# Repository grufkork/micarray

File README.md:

# 16-channel Microphone Array for Spatial Audio Recording
This is an inexpensive 16-channel MEMS microphone array for recording spatial audio made in KiCad 8.0. It can  be used for creating immersive audio/video content, locating mechanical faults, tracking moving objects in a room and more.

This design is developed for the [Build-Your-Own Ambisonic Microphone Arrays](https://github.com/AppliedAcousticsChalmers/ambisonic-microphone-arrays) project, where you can also find more information regarding processing of the resulting recordings.

The array consists of four identical boards connected in a circle, allowing for low manufacturing costs (<100$ total, assembly included). These are then placed around an acoustically occluding sphere, emulating a persons head and allowing for generating realistic spatial audio. 

The array is connected to the [MiniDSP MCHStreamer Lite](https://www.minidsp.com/products/usb-audio-interface/mchstreamer-lite) sound card which receives and digitises the 8x PDM output (the non-lite version should work too, but has not been tested). 

### File structure

| Directory           | Contents                                                                                                      |
| ------------------- | ------------------------------------------------------------------------------------------------------------- |
| micarray            | 16ch microphone array, main design. Contains KiCAD project files and some exported models and visualisations. |
| imgs                | Images for this document                                                                                      |
| micarray_8ch_camera | Unfinished 8ch version for a 360° camera.                                                                     |
| 3dcammodel          | 3D-scan of 360° camera and visualisations                                                                     |

### Ordering
Production files are generated using [JLC Fabrication Toolkit](https://github.com/bennymeg/Fabrication-Toolkit) plugin for KiCad 8.0. All parts have `LCSC Part #`-fields so they can be assembled by JLC, but I would still recommend double checking everything, in particular small & cheap components so they have not gotten low availability. The full array consists of 4 quarter pieces connected in a circle. JLC minimum order size is 5, but having an extra module at hand has proven to be useful as all our orders have always had one mic with worsened performance. Whether this is due to JLC:s manufacturing process, errors in manufacturing, damages during transport or just bad luck is not known.

### Assembly
#### Shortening the inter-board headers
*This part is not mandatory for basic function, but if you want a precise, snug fit with exact distances between each microphone it is required. There will otherwise be a small gap between each board. **

Due to the tight space constraints, the headers connecting the boards to each other need to be trimmed. First remove the plastic holding the male header pins together, preferably by locally applying heat with a hot air gun and with pliers gently but decisively sliding the softened plastic off along the pins. Using a soldering iron or similar to try to melt plastic off is not recommended, as the residual plastic will fuse with the pins and form a thin insulating surface, which then needs to be sanded off. Be carful trying to cut the plastic into smaller parts, as this might bend the pins.

You can then try connecting the boards, noting how large the gap between them is (should be a couple of millimeters). Disconnect the boards and clip off the male pins so that the boards connect flush, edge-to-edge.

#### Connecting to the MCHStreamer
On each of the boards there is a vertical 2mm 12-pin header. This is to be connected to J3 on the MCHStreamer (check page 2 of [the datasheet](https://www.minidsp.com/images/documents/Product%20Brief-MCHStreamer%20Lite.pdf)). Note how the pins are mirrored, so they can be connected "towards" each other. As such, a 2x6 pin cable can be used. Which header is used only affects which mic is #1. Specifically, the first mic on the board opposite the connector will be channel 1. 

To interface with the array, upload the 16ch PDM firmware to the MCHStreamer. 

### Technical & Mechanical Details
The 16 mics are evenly spaced in a circle with 60.743mm radius. The array is made to fit on a 60mm sphere. The M3 mounting holes are 71.692mm out, 3.2mm in diameter, 27.1° counter-clockwise relative board edge.

The mics used are the Infineon IM73D122V01. They appear to currently be the best-performing MEMS mics available, using a novel double-membrane technology. Frustratingly, these have a slightly larger footprint with a different pad order than most other similar MEMS mics on the market, so be wary if swapping them for a different model.

The `stable` branch is the main, cleaned-up version of the old development `shrinkening` branch. 

### Troubleshooting
The primary problem you may experience is massive amounts of noise on one or several channels. This appears to be caused by the clock signal from the MCHStreamer ringing (overshooting) strongly. To prevent this, a 150pF capacitor is included in the design, connected between ground and the clock input. However, if you are still experiencing problems, soldering on some additional capacitance between `GND` and `PDM_CLK-IN` on the backside of one of the inter-board headers should resolve the issue. This fix is visible in the second image above, being the two yellow wires sticking out from one of the connectors.

## 8ch version
The 8ch version is an old, untested version of the 16ch for recording spatial audio with a 360° camera. It is not tested, but might work with some extra capacitance between `GND` and `PDM_CLK-IN`.

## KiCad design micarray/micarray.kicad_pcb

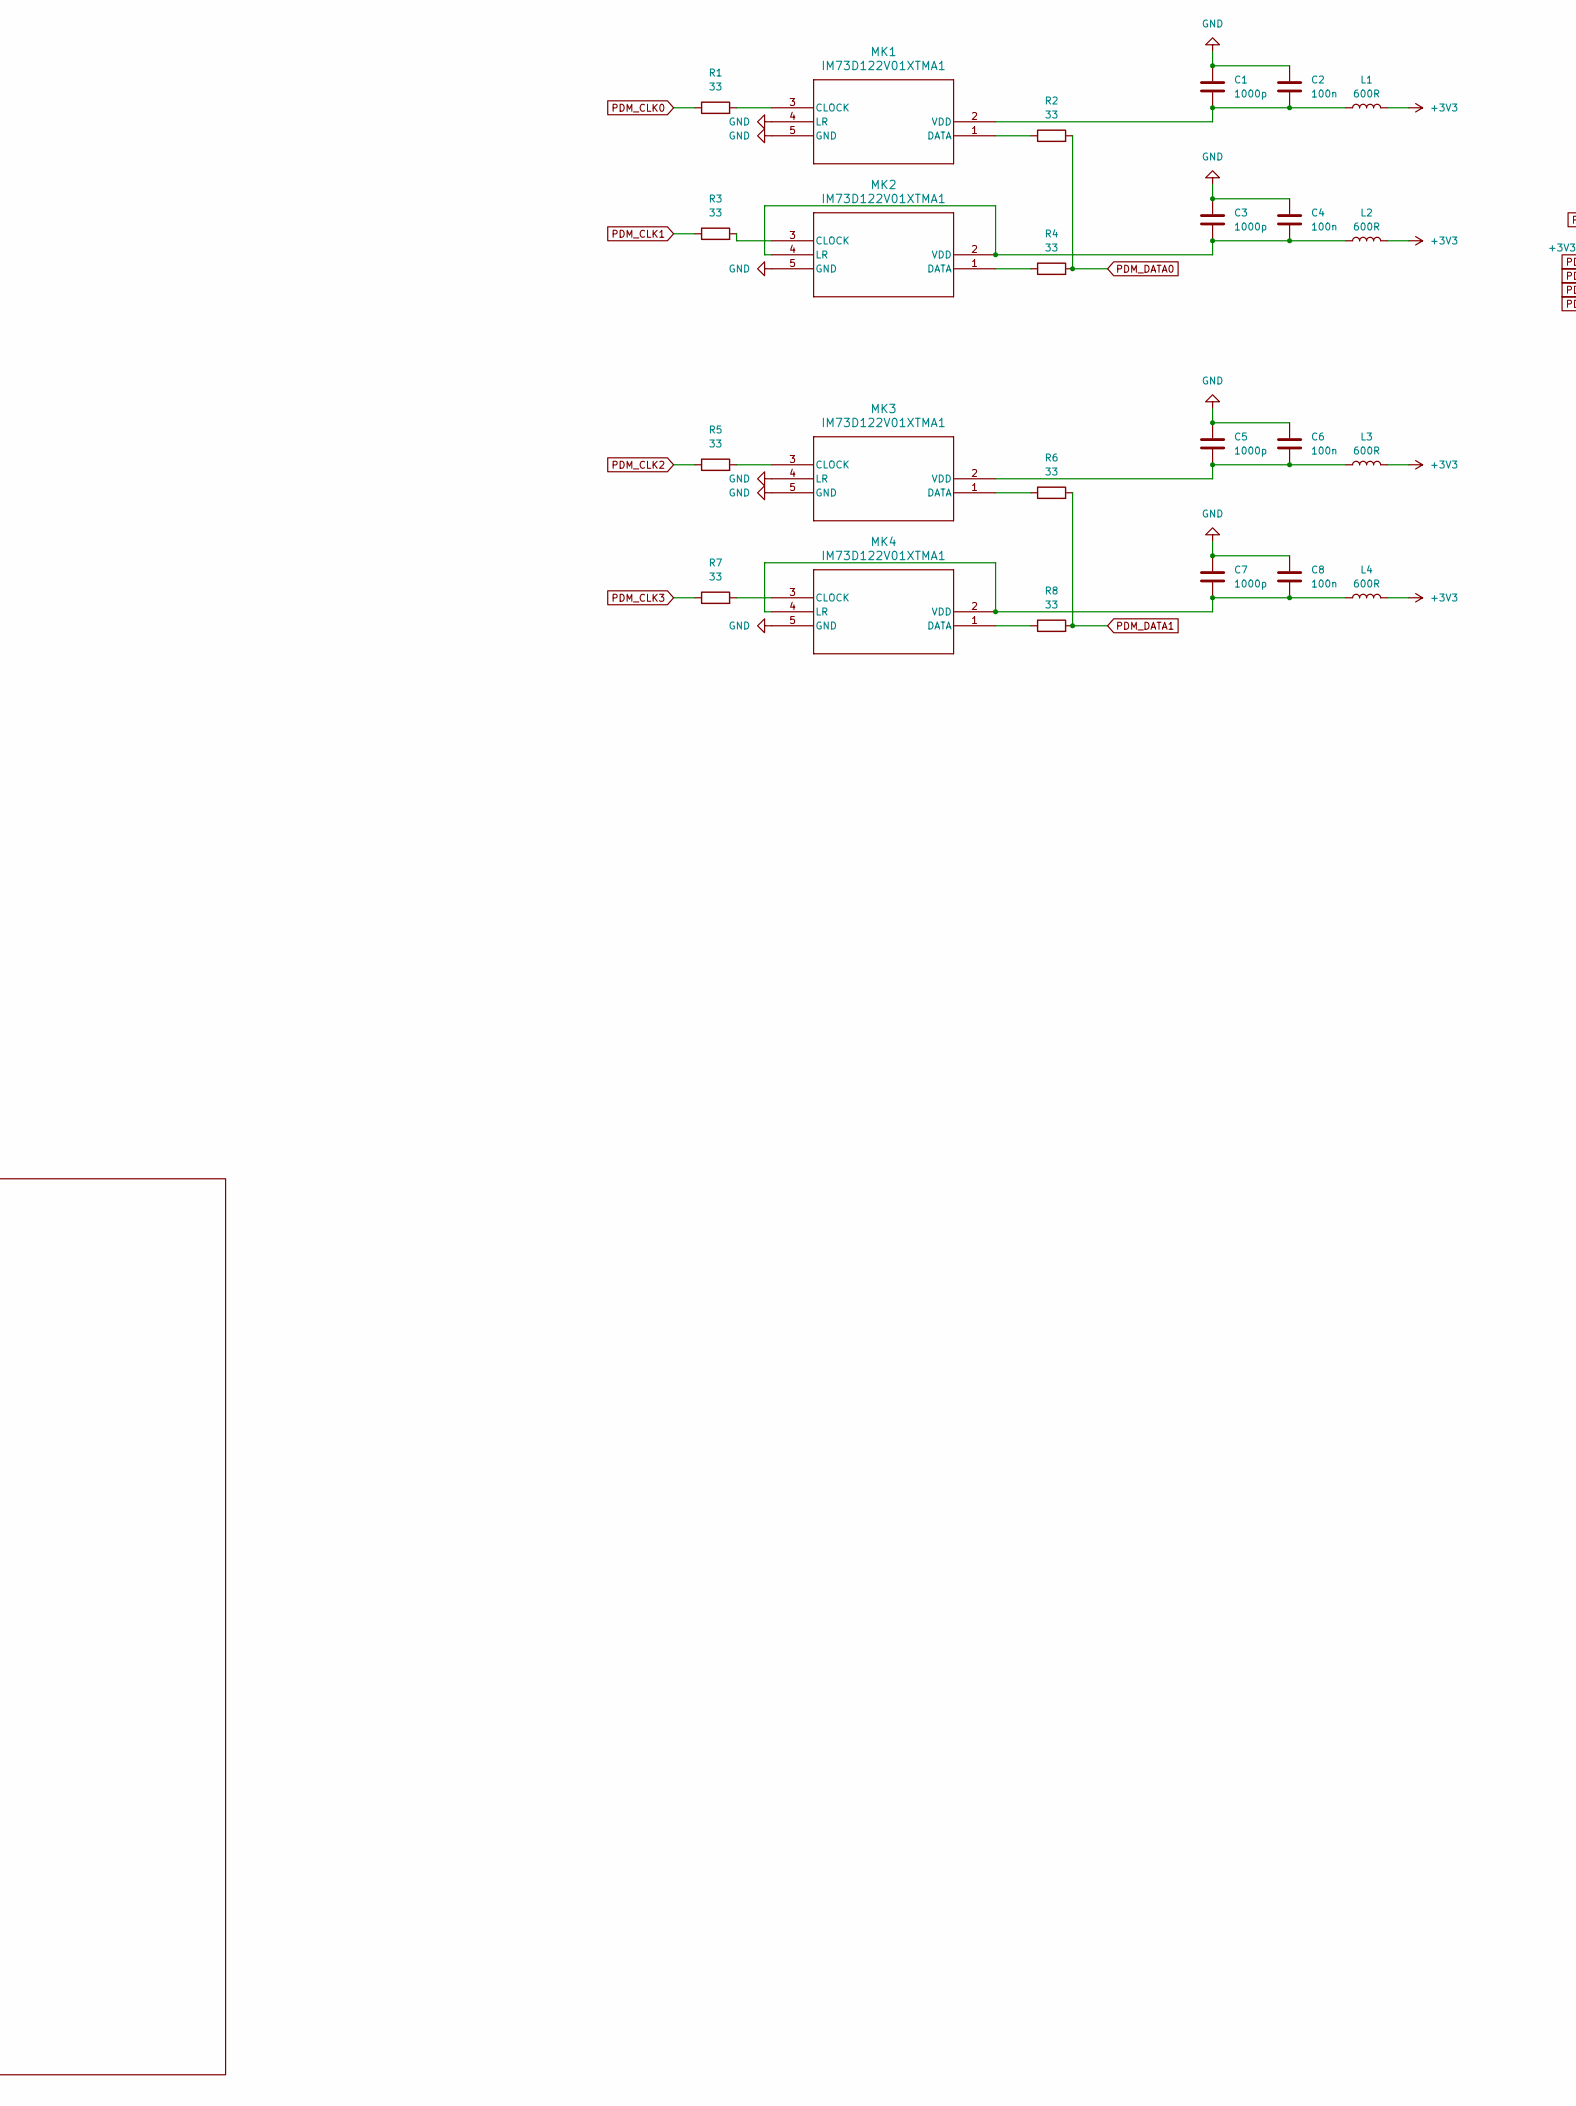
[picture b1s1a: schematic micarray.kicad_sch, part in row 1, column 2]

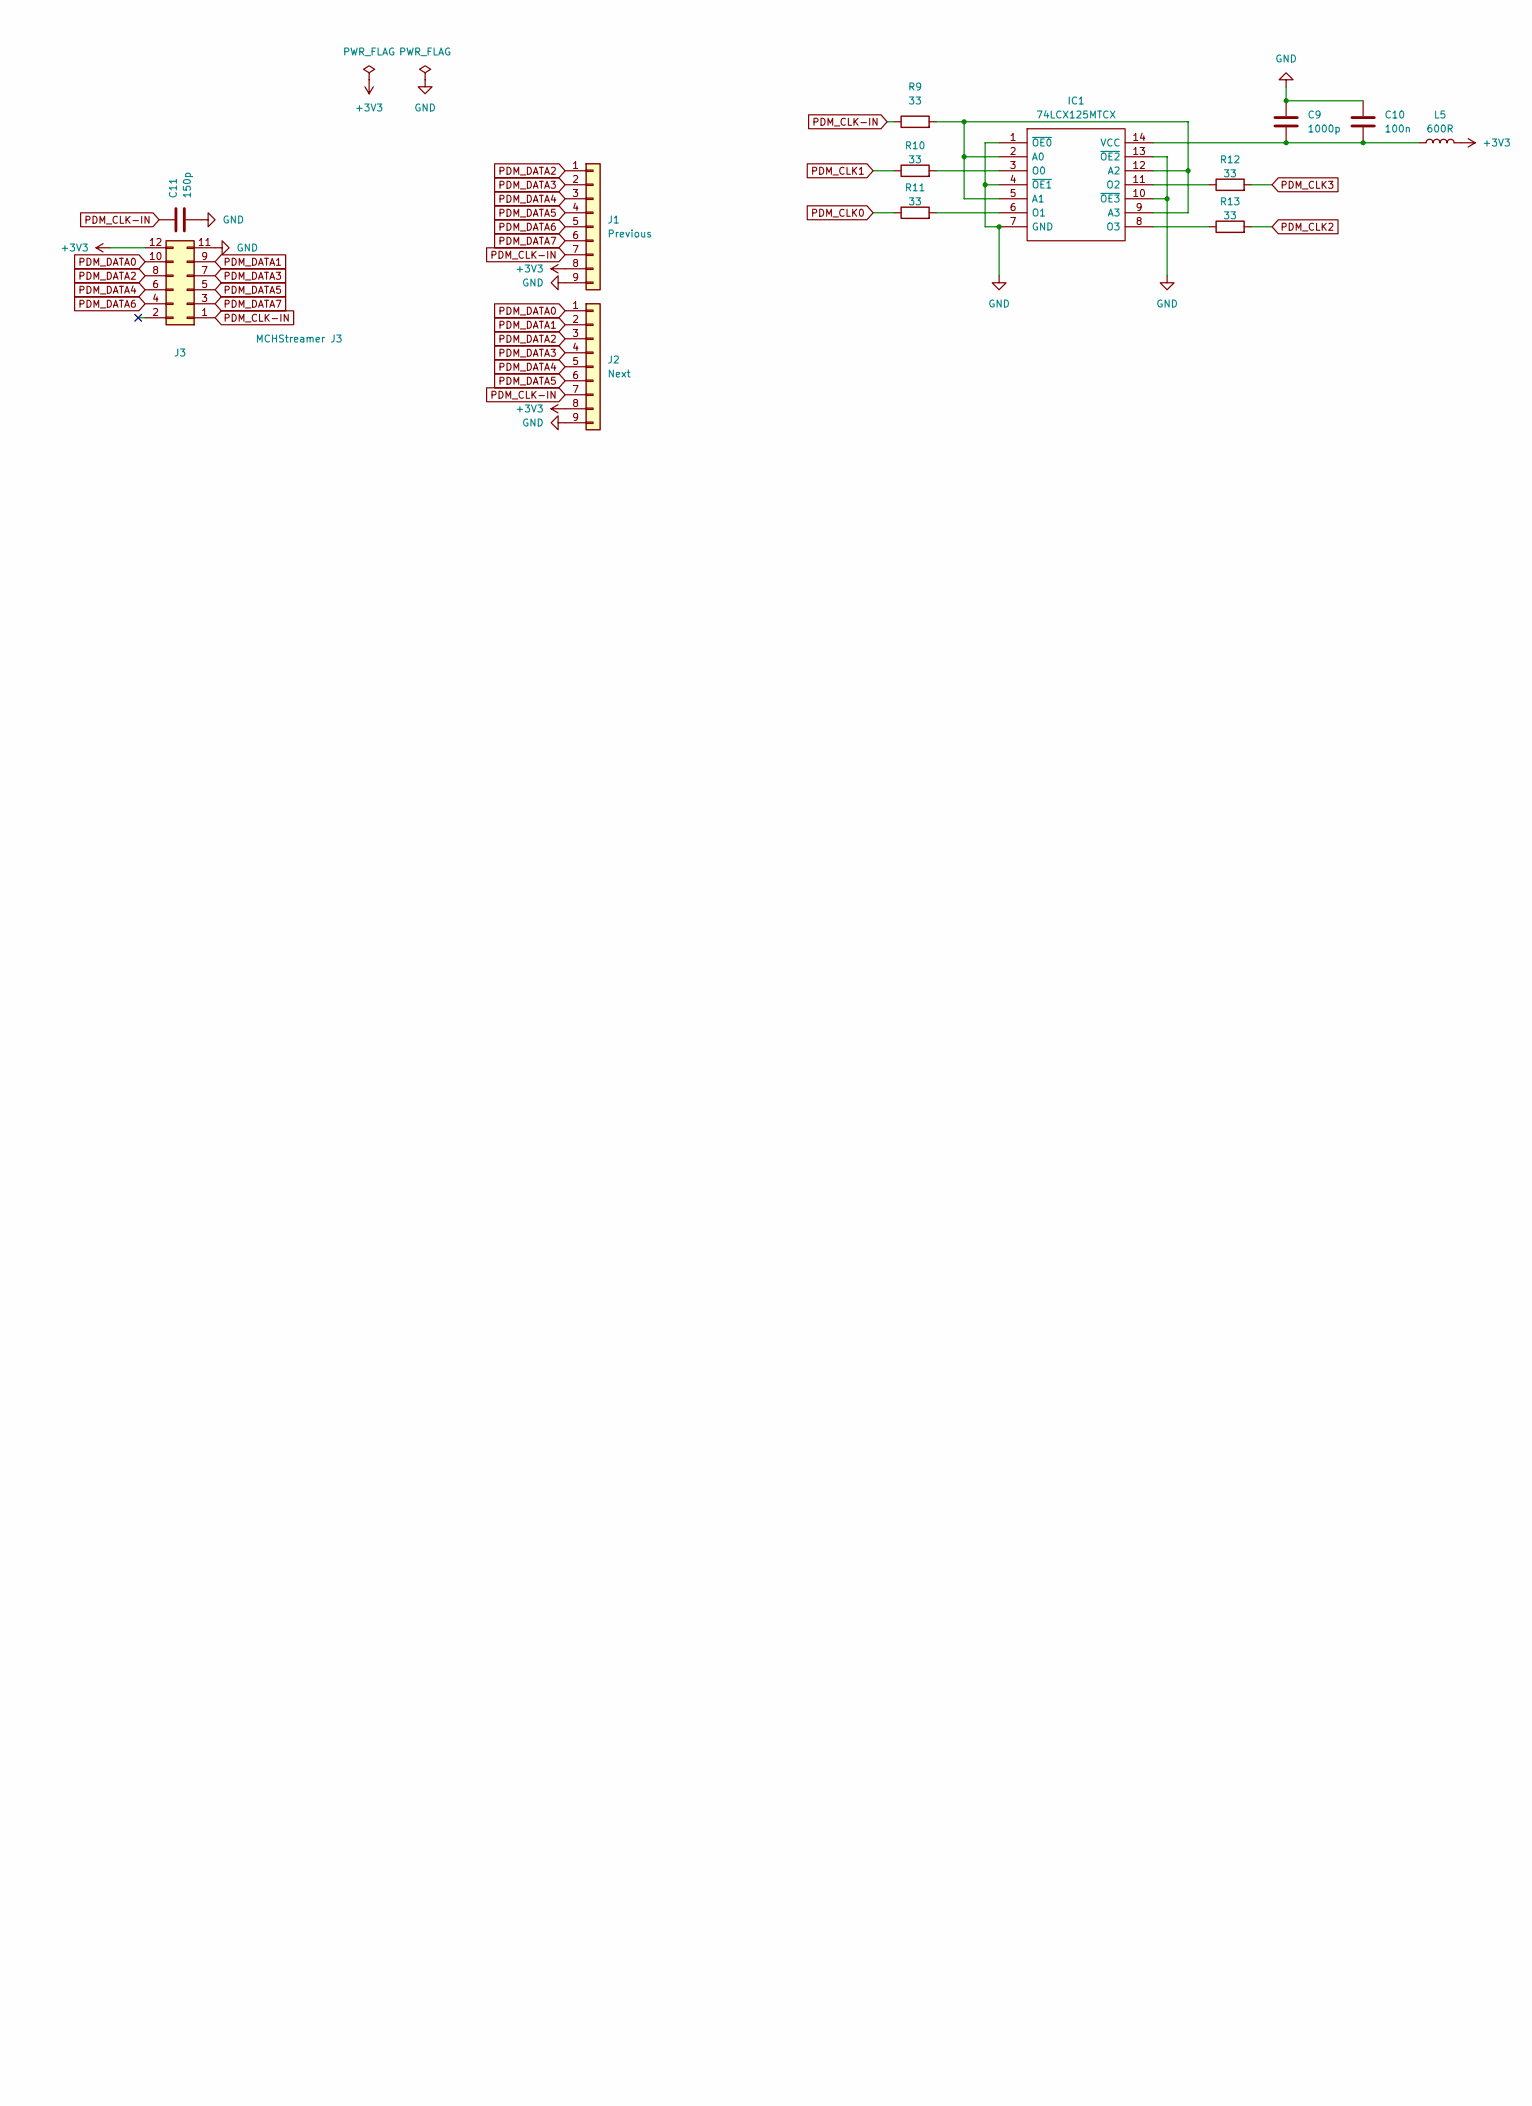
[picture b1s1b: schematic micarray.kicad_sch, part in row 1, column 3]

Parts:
C1, C3, C5, C7, C9: 1000p; C_0603_1608Metric_Pad1.08x0.95mm_HandSolder; LCSC Part # C71653
C2, C4, C6, C8, C10: 100n; C_0603_1608Metric_Pad1.08x0.95mm_HandSolder; LCSC Part # C77055
C11: 150p; C_0603_1608Metric_Pad1.08x0.95mm_HandSolder; LCSC Part # C126554
IC1: 74LCX125MTCX; TSSOP-14_4.4x5mm_P0.65mm; Mouser Part Number 512-74LCX125MTCX
J1: Previous; PinSocket_2x05_P2.54mm_Horizontal; LCSC Part # C5142480
J2: Next; PinHeader_2x05_P2.54mm_Horizontal; LCSC Part # C60563
J3: MCHStreamer J3; PinHeader_2x06_P2.00mm_Vertical; LCSC Part # C225291
L1, L2, L3, L4, L5: 600R; L_0603_1608Metric_Pad1.05x0.95mm_HandSolder; LCSC Part # C2971884
MK1, MK2, MK3, MK4: IM73D122V01XTMA1; PG-LLGA-5-2_INF; LCSC Part # C5563886
R1, R2, R3, R4, R5, R6, R7, R8, R9, R10, R11, R12, R13: 33; R_0603_1608Metric_Pad0.98x0.95mm_HandSolder; LCSC Part # C23140

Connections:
+3V3: J1.8, J2.8, J3.12, L1.2, L2.2, L3.2, L4.2, L5.2
GND: C1.1, C2.1, C3.1, C4.1, C5.1, C6.1, C7.1, C8.1, C9.1, C10.1, C11.2, IC1.1 (~OE0), IC1.4 (~OE1), IC1.7 (GND), IC1.10 (~OE3), IC1.13 (~OE2), J1.9, J2.9, J3.11, MK1.4 (LR), MK1.5 (GND), MK2.5 (GND), MK3.4 (LR), MK3.5 (GND), MK4.5 (GND)
unnamed: IC1.2 (A0), IC1.5 (A1), IC1.9 (A3), IC1.12 (A2), R9.2
unnamed: IC1.3 (O0), R10.2
unnamed: IC1.6 (O1), R11.2
unnamed: IC1.11 (O2), R12.1
unnamed: IC1.8 (O3), R13.1
unnamed: C9.2, C10.2, IC1.14 (VCC), L5.1
unnamed: MK1.3 (CLOCK), R1.2
unnamed: MK1.1 (DATA), R2.1
unnamed: C1.2, C2.2, L1.1, MK1.2 (VDD)
unnamed: MK2.3 (CLOCK), R3.2
unnamed: MK2.1 (DATA), R4.1
unnamed: C3.2, C4.2, L2.1, MK2.2 (VDD), MK2.4 (LR)
unnamed: MK3.3 (CLOCK), R5.2
unnamed: MK3.1 (DATA), R6.1
unnamed: C5.2, C6.2, L3.1, MK3.2 (VDD)
unnamed: MK4.3 (CLOCK), R7.2
unnamed: MK4.1 (DATA), R8.1
unnamed: C7.2, C8.2, L4.1, MK4.2 (VDD), MK4.4 (LR)
PDM_CLK0: R1.1, R11.1
PDM_CLK1: R3.1, R10.1
PDM_CLK2: R5.1, R13.2
PDM_CLK3: R7.1, R12.2
PDM_CLK-IN: C11.1, J1.7, J2.7, J3.1, R9.1
PDM_DATA0: J2.1, J3.10, R2.2, R4.2
PDM_DATA1: J2.2, J3.9, R6.2, R8.2
PDM_DATA2: J1.1, J2.3, J3.8
PDM_DATA3: J1.2, J2.4, J3.7
PDM_DATA4: J1.3, J2.5, J3.6
PDM_DATA5: J1.4, J2.6, J3.5
PDM_DATA6: J1.5, J3.4
PDM_DATA7: J1.6, J3.3

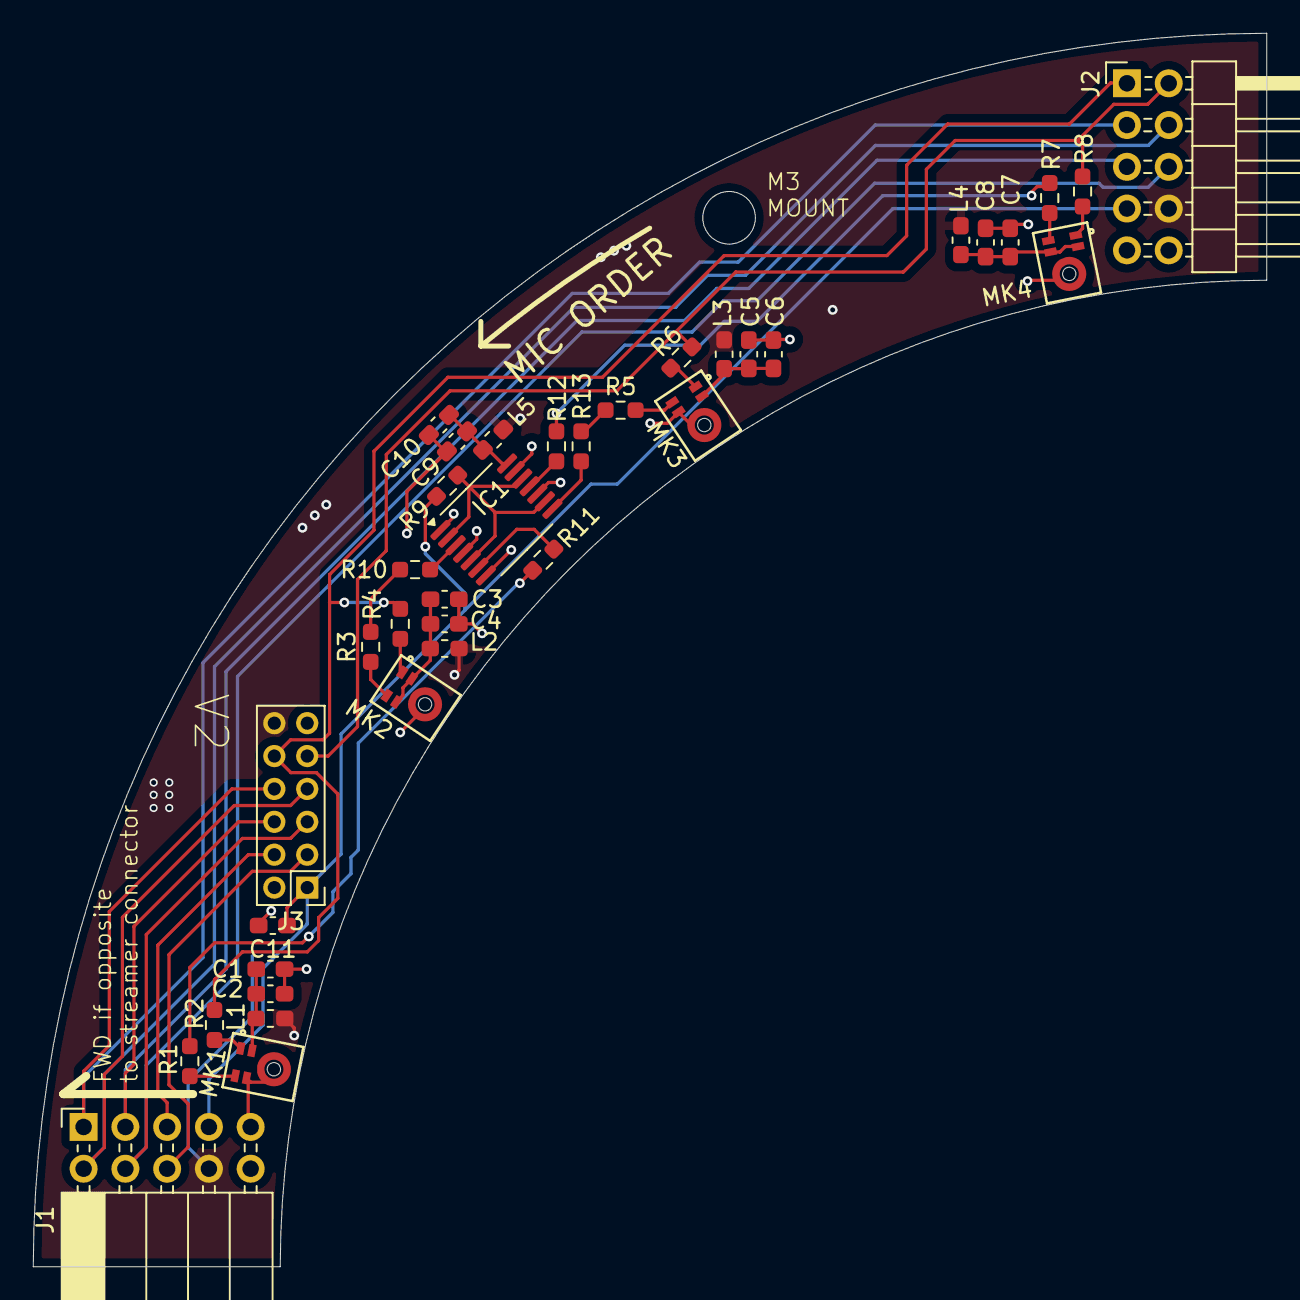
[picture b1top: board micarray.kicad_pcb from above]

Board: 4 copper layers, 75.0 x 75.0 mm, 37 parts (0 on the bottom side), 33 nets.

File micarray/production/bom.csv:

Designator,Footprint,Quantity,Value,LCSC Part #
"C1, C3, C5, C7, C9",0603,5,1000p,C71653
"C10, C2, C4, C6, C8",0603,5,100n,C77055
C11,0603,1,20p,C126554
IC1,TSSOP-14_4.4x5mm_P0.65mm,1,74LCX125MTCX,C141450
J1,PinSocket_2x05_P2.54mm_Horizontal,1,Previous,C5142480
J2,PinHeader_2x05_P2.54mm_Horizontal,1,Next,C60563
J3,PinHeader_2x06_P2.00mm_Vertical,1,MCHStreamer J3,C225291
"L1, L2, L3, L4, L5",0603,5,600R,C2971884
"MK1, MK2, MK3, MK4",PG-LLGA-5-2_INF,4,IM73D122V01XTMA1,C5563886
"R1, R10, R11, R12, R13, R2, R3, R4, R5, R6, R7, R8, R9",0603,13,33,C23140

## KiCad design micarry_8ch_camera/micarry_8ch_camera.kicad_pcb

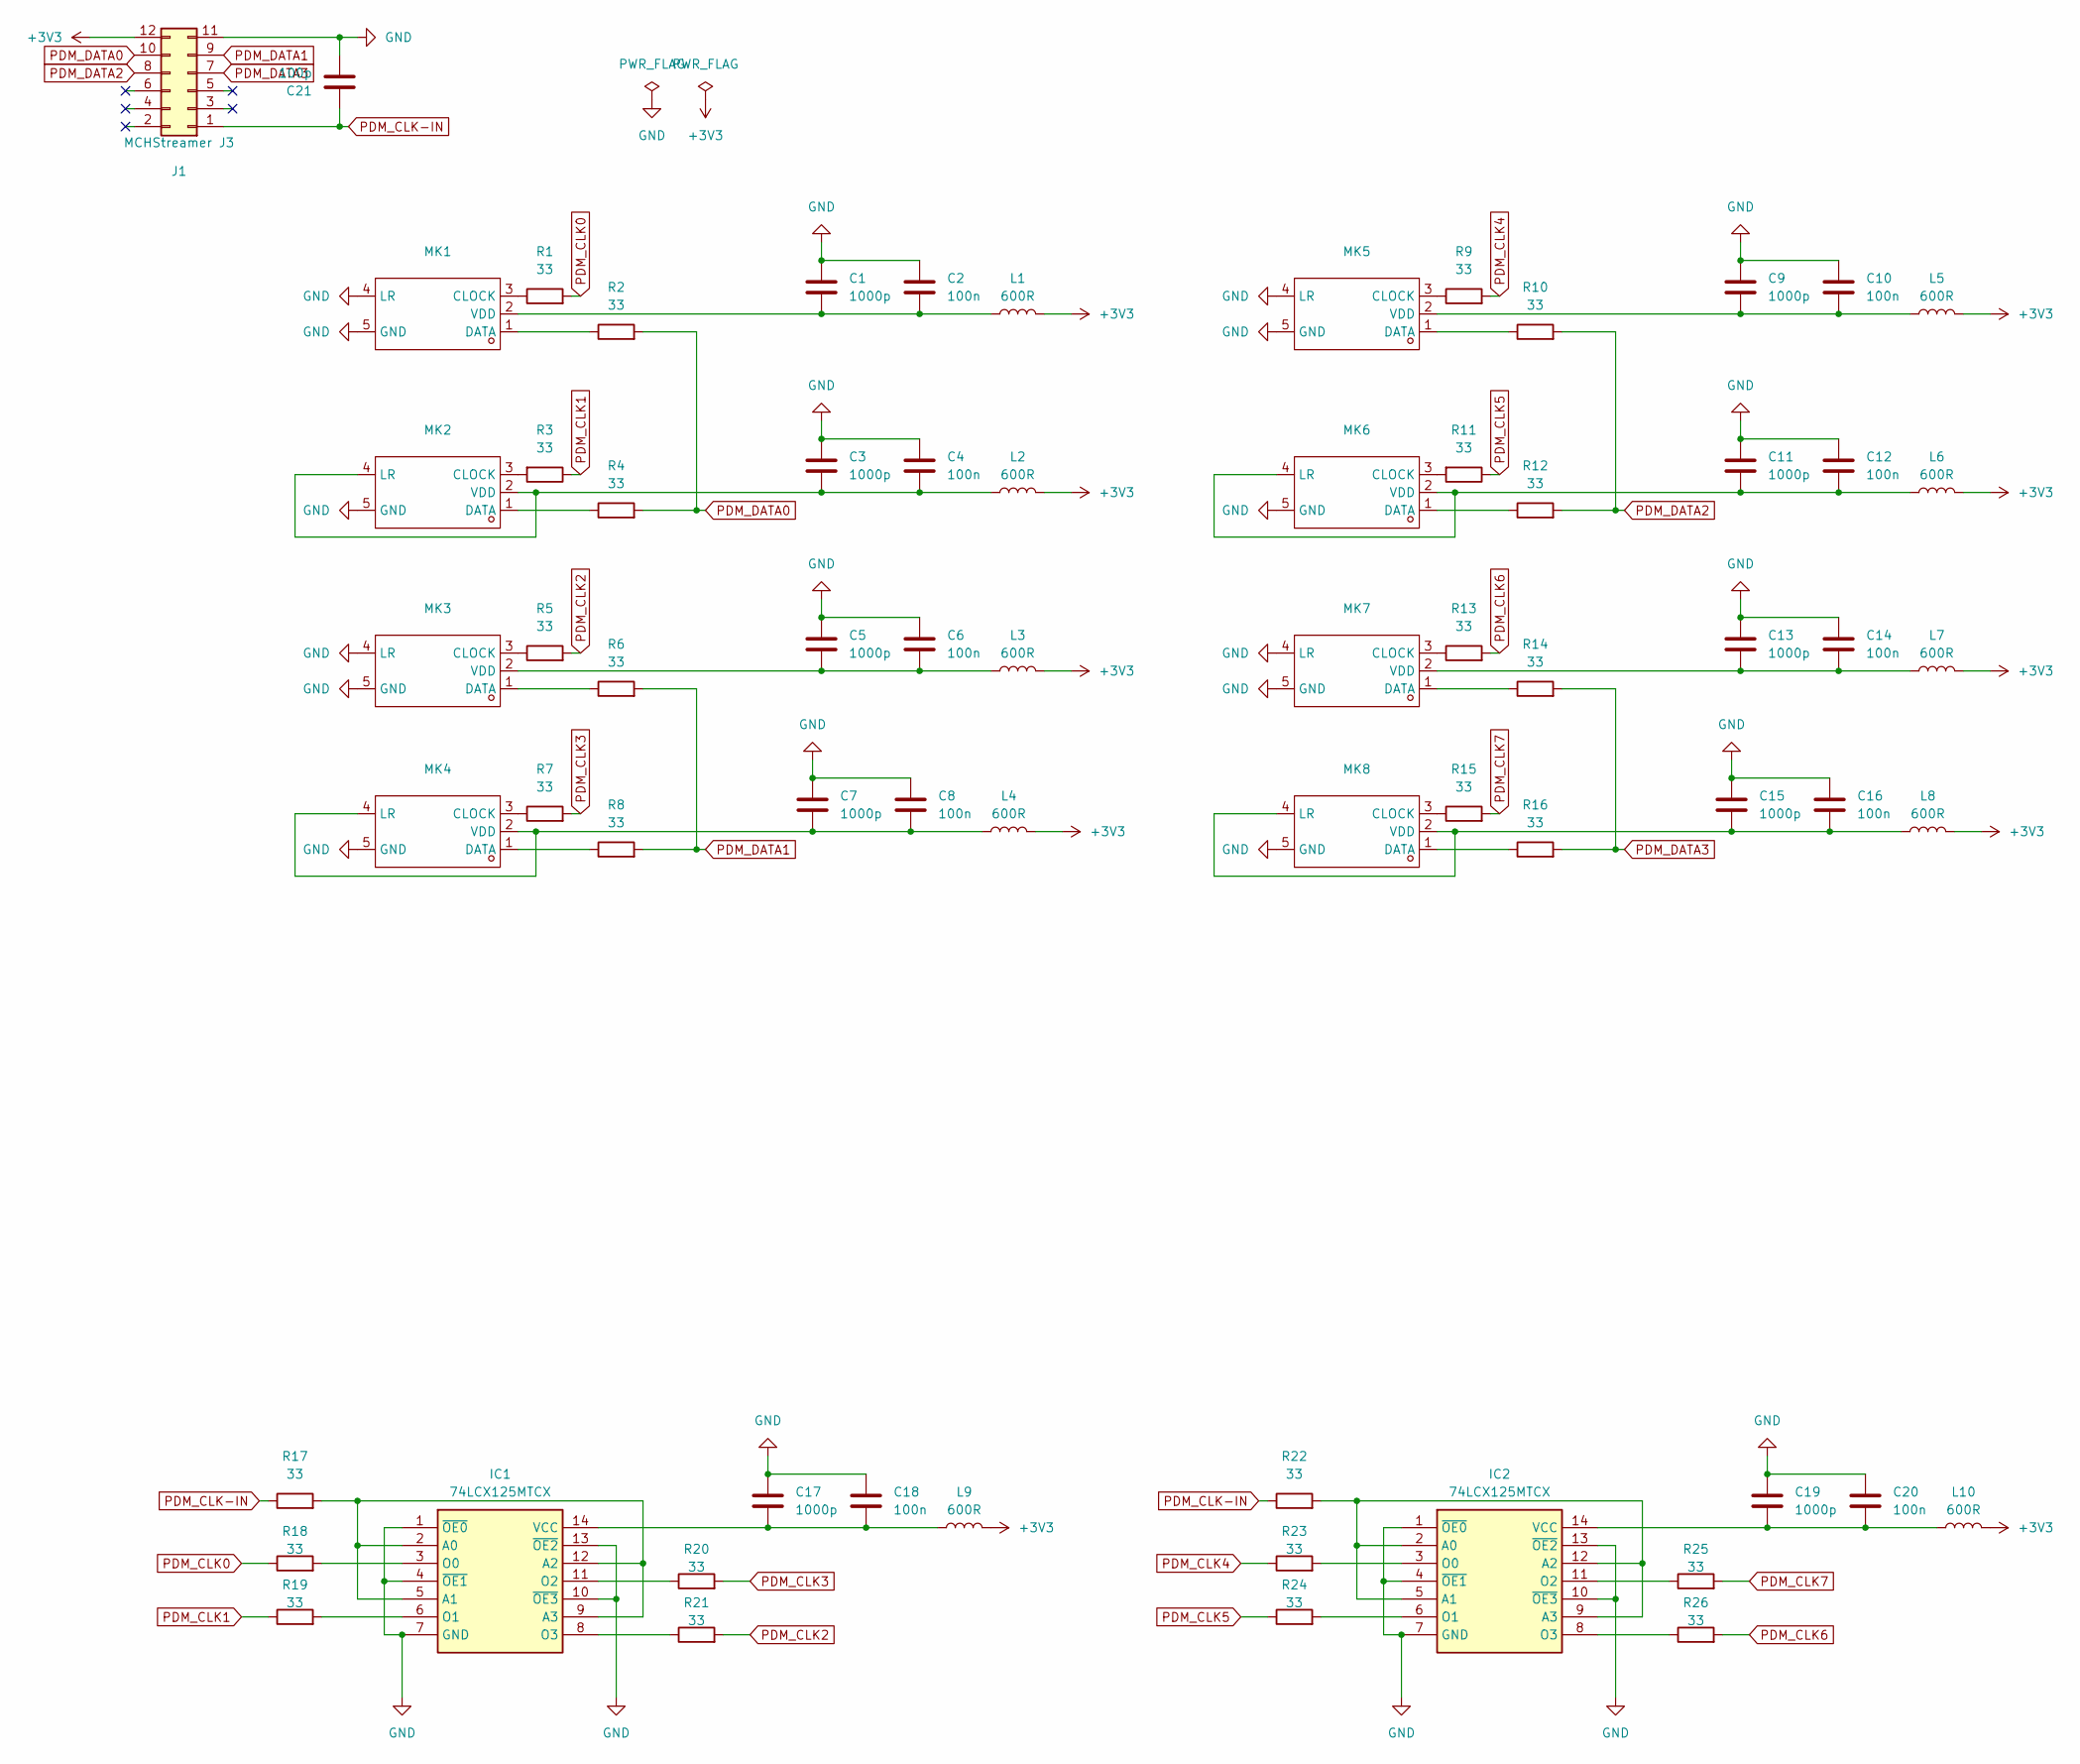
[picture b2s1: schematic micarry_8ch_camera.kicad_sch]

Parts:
C1, C3, C5, C7, C9, C11, C13, C15, C17, C19: 1000p; C_0603_1608Metric_Pad1.08x0.95mm_HandSolder; LCSC Part # C71653
C2, C4, C6, C8, C10, C12, C14, C16, C18, C20: 100n; C_0603_1608Metric_Pad1.08x0.95mm_HandSolder; LCSC Part # C77055
C21: 100p; C_0603_1608Metric_Pad1.08x0.95mm_HandSolder; LCSC Part # C71653
IC1, IC2: 74LCX125MTCX; TSSOP-14_4.4x5mm_P0.65mm; Mouser Part Number 512-74LCX125MTCX
J1: MCHStreamer J3; PinHeader_2x06_P2.00mm_Vertical; LCSC Part # C60565
L1, L2, L3, L4, L5, L6, L7, L8, L9, L10: 600R; L_0603_1608Metric_Pad1.05x0.95mm_HandSolder; LCSC Part # C2971884
MK1, MK2, MK3, MK4, MK5, MK6, MK7, MK8: PG-LLGA-5-2_INF
R1, R2, R3, R4, R5, R6, R7, R8, R9, R10, R11, R12, R13, R14, R15, R16, R17, R18, R19, R20, R21, R22, R23, R24, R25, R26: 33; R_0603_1608Metric_Pad0.98x0.95mm_HandSolder

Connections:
+3V3: J1.12, L1.2, L2.2, L3.2, L4.2, L5.2, L6.2, L7.2, L8.2, L9.2, L10.2
GND: C1.1, C2.1, C3.1, C4.1, C5.1, C6.1, C7.1, C8.1, C9.1, C10.1, C11.1, C12.1, C13.1, C14.1, C15.1, C16.1, C17.1, C18.1, C19.1, C20.1, C21.2, IC1.1 (~OE0), IC1.4 (~OE1), IC1.7 (GND), IC1.10 (~OE3), IC1.13 (~OE2), IC2.1 (~OE0), IC2.4 (~OE1), IC2.7 (GND), IC2.10 (~OE3), IC2.13 (~OE2), J1.11, MK1.4 (LR), MK1.5 (GND), MK2.5 (GND), MK3.4 (LR), MK3.5 (GND), MK4.5 (GND), MK5.4 (LR), MK5.5 (GND), MK6.5 (GND), MK7.4 (LR), MK7.5 (GND), MK8.5 (GND)
unnamed: IC1.2 (A0), IC1.5 (A1), IC1.9 (A3), IC1.12 (A2), R17.2
unnamed: IC1.3 (O0), R18.2
unnamed: IC1.6 (O1), R19.2
unnamed: IC1.11 (O2), R20.1
unnamed: IC1.8 (O3), R21.1
unnamed: C17.2, C18.2, IC1.14 (VCC), L9.1
unnamed: IC2.2 (A0), IC2.5 (A1), IC2.9 (A3), IC2.12 (A2), R22.2
unnamed: IC2.3 (O0), R23.2
unnamed: IC2.6 (O1), R24.2
unnamed: IC2.11 (O2), R25.1
unnamed: IC2.8 (O3), R26.1
unnamed: C19.2, C20.2, IC2.14 (VCC), L10.1
unnamed: MK1.3 (CLOCK), R1.1
unnamed: MK1.1 (DATA), R2.1
unnamed: C1.2, C2.2, L1.1, MK1.2 (VDD)
unnamed: MK2.3 (CLOCK), R3.2
unnamed: MK2.1 (DATA), R4.1
unnamed: C3.2, C4.2, L2.1, MK2.2 (VDD), MK2.4 (LR)
unnamed: MK3.3 (CLOCK), R5.1
unnamed: MK3.1 (DATA), R6.1
unnamed: C5.2, C6.2, L3.1, MK3.2 (VDD)
unnamed: MK4.3 (CLOCK), R7.1
unnamed: MK4.1 (DATA), R8.1
unnamed: C7.2, C8.2, L4.1, MK4.2 (VDD), MK4.4 (LR)
unnamed: MK5.3 (CLOCK), R9.1
unnamed: MK5.1 (DATA), R10.1
unnamed: C9.2, C10.2, L5.1, MK5.2 (VDD)
unnamed: MK6.3 (CLOCK), R11.2
unnamed: MK6.1 (DATA), R12.1
unnamed: C11.2, C12.2, L6.1, MK6.2 (VDD), MK6.4 (LR)
unnamed: MK7.3 (CLOCK), R13.1
unnamed: MK7.1 (DATA), R14.1
unnamed: C13.2, C14.2, L7.1, MK7.2 (VDD)
unnamed: MK8.3 (CLOCK), R15.1
unnamed: MK8.1 (DATA), R16.1
unnamed: C15.2, C16.2, L8.1, MK8.2 (VDD), MK8.4 (LR)
PDM_CLK0: R1.2, R18.1
PDM_CLK1: R3.1, R19.1
PDM_CLK2: R5.2, R21.2
PDM_CLK3: R7.2, R20.2
PDM_CLK4: R9.2, R23.1
PDM_CLK5: R11.1, R24.1
PDM_CLK6: R13.2, R26.2
PDM_CLK7: R15.2, R25.2
PDM_CLK-IN: C21.1, J1.1, R17.1, R22.1
PDM_DATA0: J1.10, R2.2, R4.2
PDM_DATA1: J1.9, R6.2, R8.2
PDM_DATA2: J1.8, R10.2, R12.2
PDM_DATA3: J1.7, R14.2, R16.2

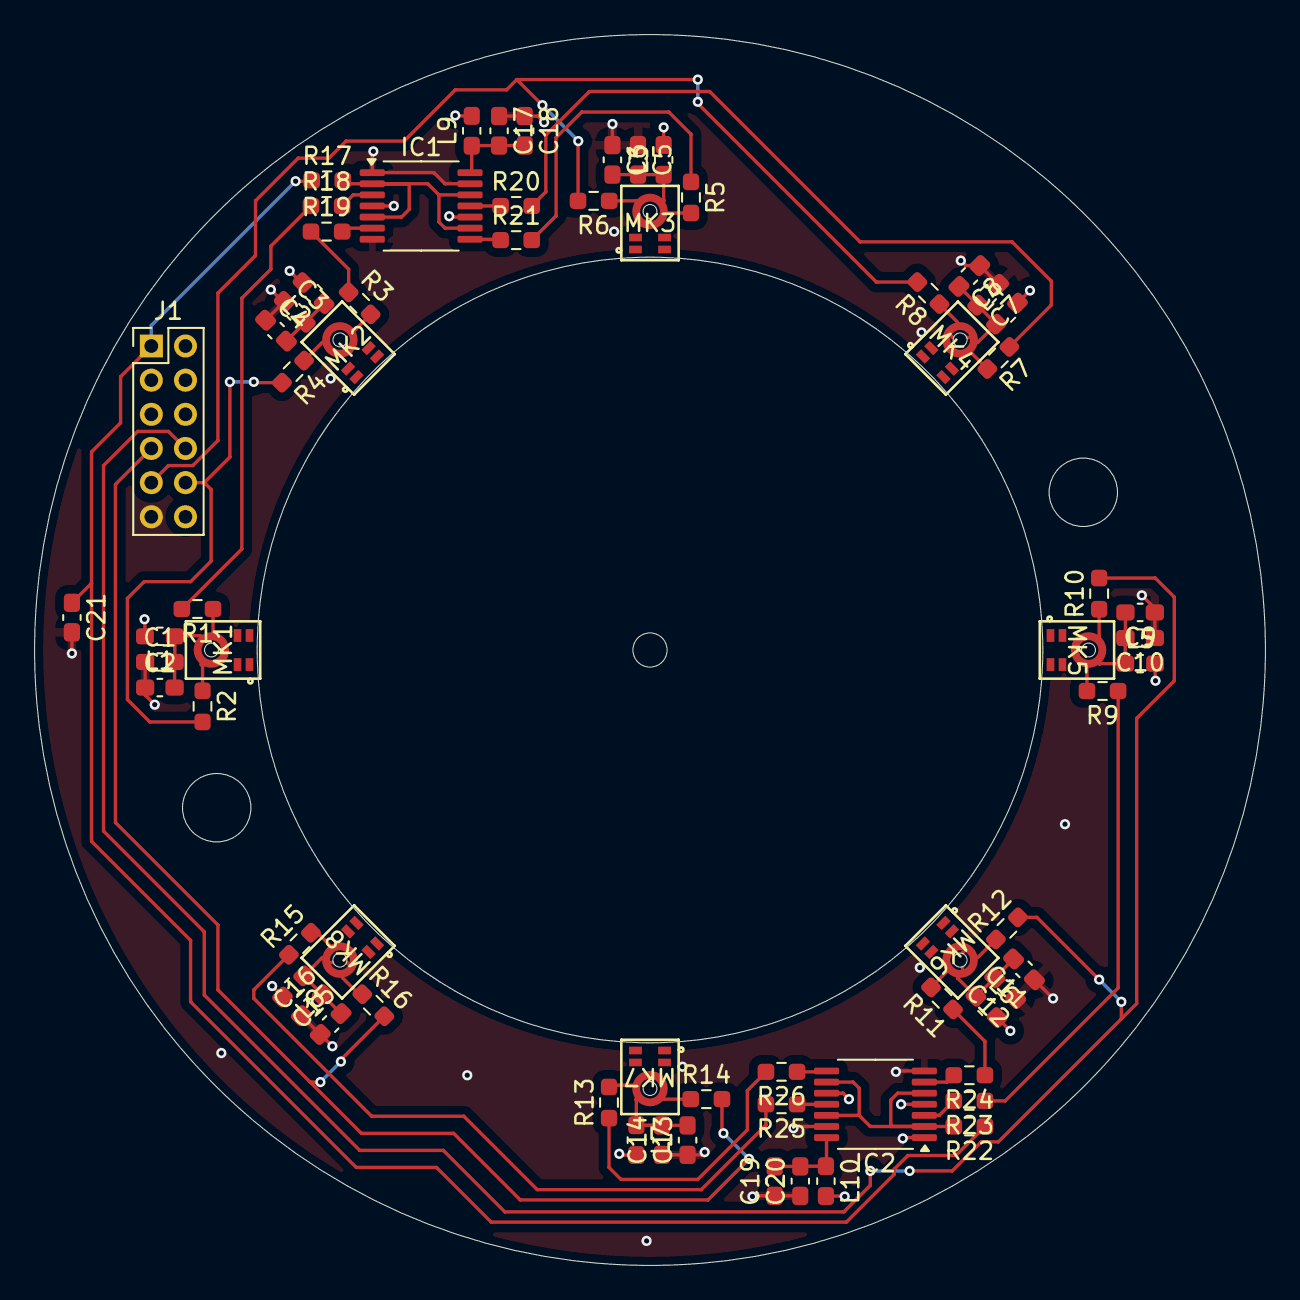
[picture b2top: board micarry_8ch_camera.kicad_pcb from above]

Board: 4 copper layers, 72.1 x 72.1 mm, 68 parts (0 on the bottom side), 51 nets.

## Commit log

2024-06-07 save
2024-06-10 All traces, no ground to mic
2024-06-10 Mic GND connection, silkscreen cleanup
2024-06-13 JLC IDs added, pre TSSOP14
2024-06-13 Change Mic and IC footprint
2024-06-23 Version 1 ordered
2024-07-08 3D-scan of small 360 camera
2024-07-08 Troubleshooting
2024-07-23 mounting hole
2024-08-08 8ch progress, new mics for 16ch
2024-08-11 16ch V2 ordered
2024-08-12 Clock line capacitor was in the wrong place
2024-11-24 Save before dev-fork
2024-11-24 Cleanup, library move
2024-11-24 8ch: update library location
2024-11-24 Add connector image
2024-11-24 Rename
2024-12-05 New images
2024-12-19 Create LICENSE
